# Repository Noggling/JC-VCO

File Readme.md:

# Analog JC Oscillator

Speck for JS Oscillator v1. The first version should be  a proof of concept. Containing a limited amount of features

## Contents

- [Analog JC Oscillator](#analog-jc-oscillator)
  - [Contents](#contents)
  - [Links](#links)
  - [Resources References](#resources-references)

## Links

- [Requirements](./JS-VCO-Requirements.md)
- [JS-VCO Oscillator](./JS-VCO-Oscillator.md)
- [JS-VCO OneVoltOctave](./JC-VCO-OneVoltOctave.md)

- 1v/oct tracing for pitch.
- Core Frequency Adjustment
- Fine Frequency Adjustment
- FM modulation
- PWM Puls With Modulation
  
## Outputs

# Ideas

## Waveshaping through "cheats"

Adjustable Half wave rectifier can be used to fold a Saw into a triangle by reflecting the top by inverting the "overflow" input. This can be achieved by adjusting the amplification of the saw output.

<!-- ## About -->

<!-- TODO -->
## Resources References

<!-- # Build Guide -->

<!-- TODO -->

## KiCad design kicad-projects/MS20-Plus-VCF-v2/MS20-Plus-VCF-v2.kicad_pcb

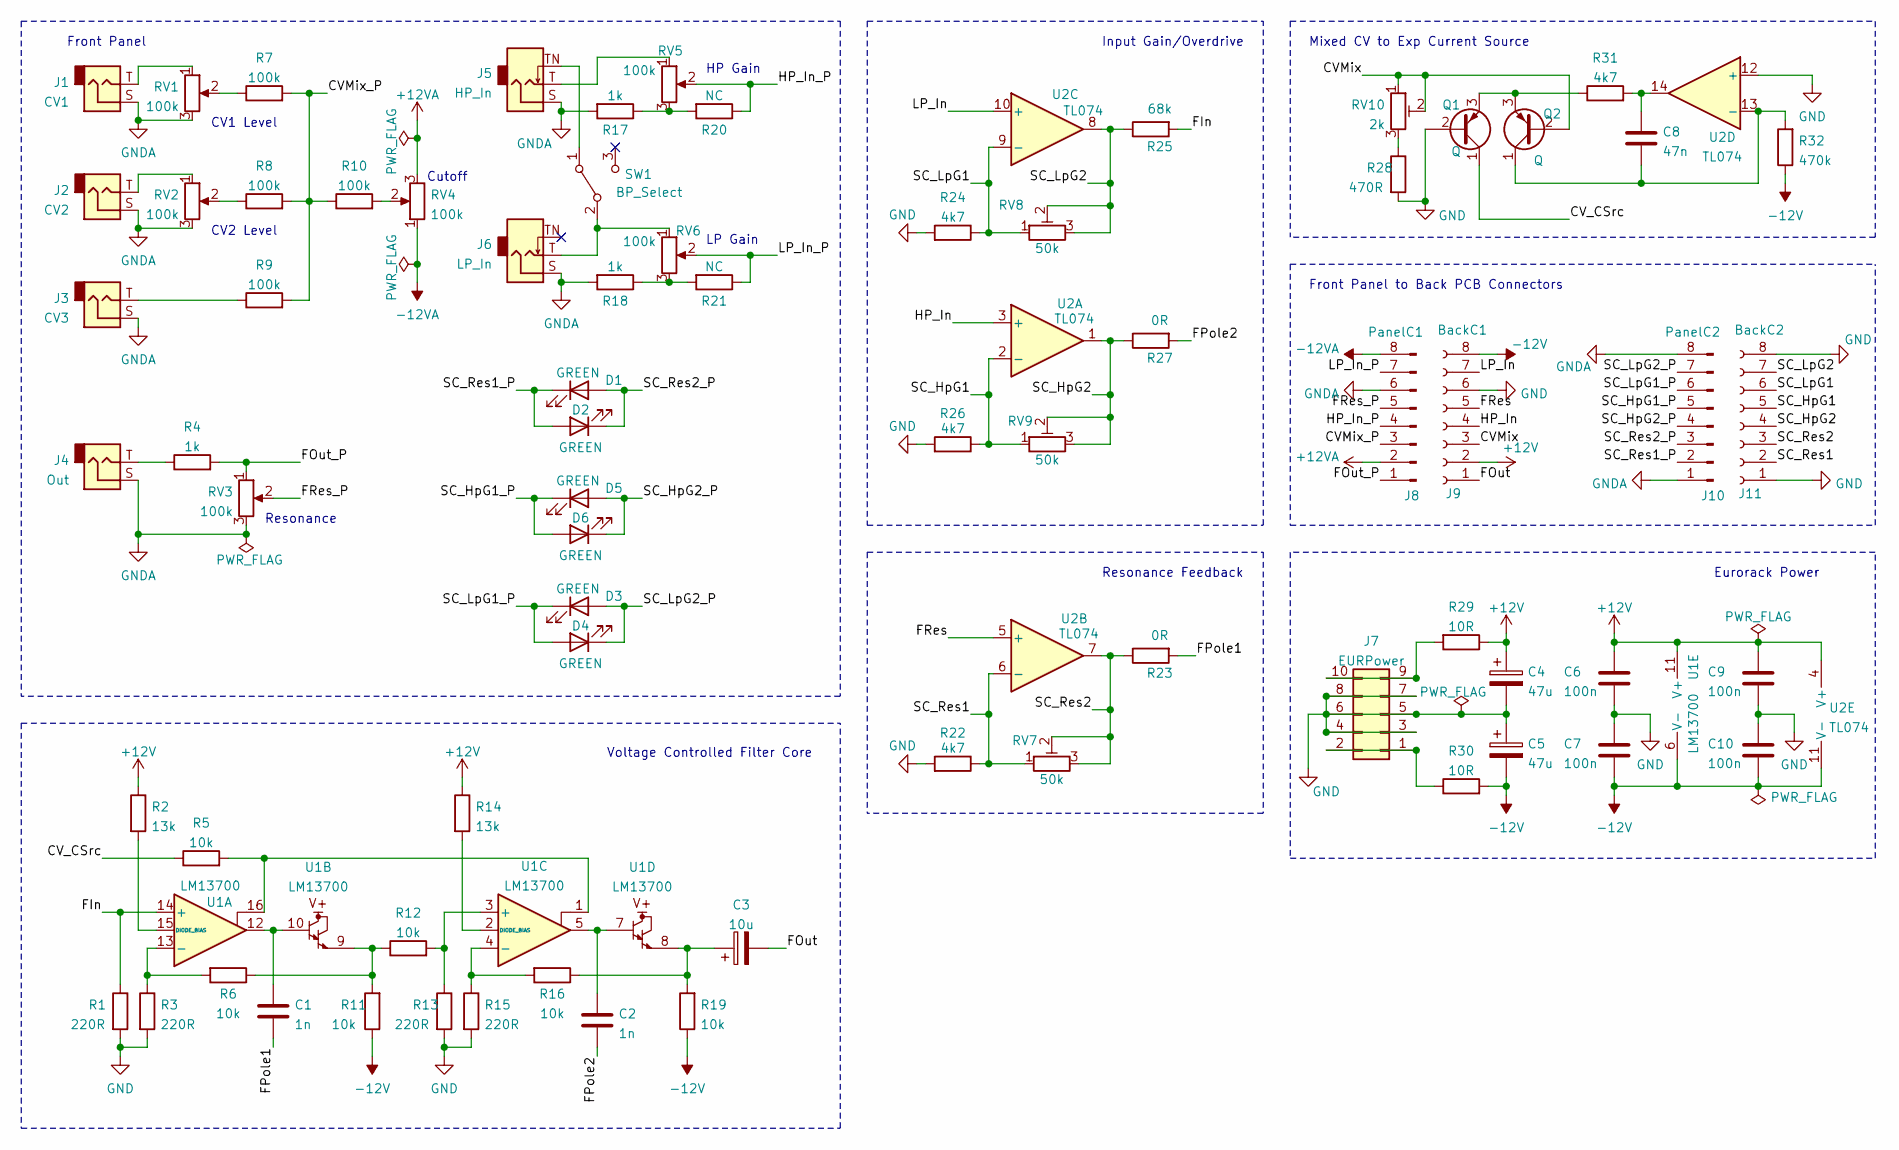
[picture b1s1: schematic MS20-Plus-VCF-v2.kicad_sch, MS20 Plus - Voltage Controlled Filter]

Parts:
C1, C2: 1n; C_Rect_L7.0mm_W3.5mm_P5.00mm
C3: 10u; CP_Radial_D5.0mm_P2.50mm
C4, C5: 47u; CP_Radial_D6.3mm_P2.50mm
C6, C7, C9, C10: 100n; C_Rect_L7.0mm_W3.5mm_P5.00mm
C8: 47n; C_Rect_L7.0mm_W3.5mm_P5.00mm
D1, D2, D3, D4, D5, D6: GREEN; LED_D3.0mm
J1: CV1; Jack_3.5mm_QingPu_WQP-PJ398SM_Vertical_CircularHoles
J2: CV2; Jack_3.5mm_QingPu_WQP-PJ398SM_Vertical_CircularHoles
J3: CV3; Jack_3.5mm_QingPu_WQP-PJ398SM_Vertical_CircularHoles
J4: Out; Jack_3.5mm_QingPu_WQP-PJ398SM_Vertical_CircularHoles
J5: HP_In; Jack_3.5mm_QingPu_WQP-PJ398SM_Vertical_CircularHoles
J6: LP_In; Jack_3.5mm_QingPu_WQP-PJ398SM_Vertical_CircularHoles
J7: EURPower; IDC-Header_2x05_P2.54mm_Vertical
J8: PanelC1; PinHeader_1x08_P2.54mm_Vertical
J9: BackC1; PinSocket_1x08_P2.54mm_Vertical
J10: PanelC2; PinHeader_1x08_P2.54mm_Vertical
J11: BackC2; PinSocket_1x08_P2.54mm_Vertical
Q1, Q2: Q; TO-92_Inline
R1, R3, R13, R15: 220R; R_Axial_DIN0207_L6.3mm_D2.5mm_P7.62mm_Horizontal
R2, R14: 13k; R_Axial_DIN0207_L6.3mm_D2.5mm_P7.62mm_Horizontal
R4, R17, R18: 1k; R_Axial_DIN0207_L6.3mm_D2.5mm_P7.62mm_Horizontal
R5, R6, R11, R12, R16, R19: 10k; R_Axial_DIN0207_L6.3mm_D2.5mm_P7.62mm_Horizontal
R7, R8, R9, R10: 100k; R_Axial_DIN0207_L6.3mm_D2.5mm_P7.62mm_Horizontal
R20, R21: NC; R_Axial_DIN0207_L6.3mm_D2.5mm_P7.62mm_Horizontal
R22, R24, R26, R31: 4k7; R_Axial_DIN0207_L6.3mm_D2.5mm_P7.62mm_Horizontal
R23, R27: 0R; R_Axial_DIN0207_L6.3mm_D2.5mm_P7.62mm_Horizontal
R25: 68k; R_Axial_DIN0207_L6.3mm_D2.5mm_P7.62mm_Horizontal
R28: 470R; R_Axial_DIN0207_L6.3mm_D2.5mm_P7.62mm_Horizontal
R29, R30: 10R; R_Axial_DIN0207_L6.3mm_D2.5mm_P7.62mm_Horizontal
R32: 470k; R_Axial_DIN0207_L6.3mm_D2.5mm_P7.62mm_Horizontal
RV1, RV2, RV3, RV4, RV5, RV6: 100k; Potentiometer_Alpha_RD901F-40-00D_Single_Vertical
RV7, RV8, RV9: 50k; Potentiometer_Bourns_3296W_Vertical
RV10: 2k; Potentiometer_Bourns_3296W_Vertical
SW1: BP_Select; 5mm_rocker_toggle_switch
U1: LM13700; DIP-16_W7.62mm
U2: TL074; DIP-14_W7.62mm

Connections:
+12V: C4.1, C6.1, C9.1, J9.2, R2.1, R14.1, R29.1, U1.11 (V+), U2.4 (V+)
+12VA: J8.2, RV4.3
-12V: C5.2, C7.2, C10.2, J9.8, R11.1, R19.1, R30.2, R32.1, U1.6 (V-), U2.11 (V-)
-12VA: J8.8, RV4.1
/CVMix: J9.3, Q2.2 (B), RV10.1, RV10.2
/CVMix_P: J8.3, R7.2, R8.2, R9.2, R10.1
/CV_CSrc: Q1.1 (C), R5.1
/FIn: R1.1, R25.2, U1.14 (+)
/FOut: C3.2, J9.1
/FOut_P: J8.1, R4.2, RV3.1
/FPole1: C1.2, R23.2
/FPole2: C2.2, R27.2
/FRes: J9.5, U2.5 (+)
/FRes_P: J8.5, RV3.2
/HP_In: J9.4, U2.3 (+)
/HP_In_P: J8.4, R20.1, RV5.2
/LP_In: J9.7, U2.10 (+)
/LP_In_P: J8.7, R21.1, RV6.2
/SC_HpG1: J11.5, R26.1, RV9.1, U2.2 (-)
/SC_HpG1_P: D5.1 (K), D6.2 (A), J10.5
/SC_HpG2: J11.4, R27.1, RV9.2, RV9.3, U2.1
/SC_HpG2_P: D5.2 (A), D6.1 (K), J10.4
/SC_LpG1: J11.6, R24.1, RV8.1, U2.9 (-)
/SC_LpG1_P: D3.1 (K), D4.2 (A), J10.6
/SC_LpG2: J11.7, R25.1, RV8.2, RV8.3, U2.8
/SC_LpG2_P: D3.2 (A), D4.1 (K), J10.7
/SC_Res1: J11.2, R22.1, RV7.1, U2.6 (-)
/SC_Res1_P: D1.1 (K), D2.2 (A), J10.2
/SC_Res2: J11.3, R23.1, RV7.2, RV7.3, U2.7
/SC_Res2_P: D1.2 (A), D2.1 (K), J10.3
GND: C4.2, C5.1, C6.2, C7.1, C9.2, C10.1, J7.3, J7.4, J7.5, J7.6, J7.7, J7.8, J9.6, J11.1, J11.8, Q1.2 (B), R1.2, R3.2, R13.2, R15.2, R22.2, R24.2, R26.2, R28.2, U2.12 (+)
GNDA: J1.S, J2.S, J3.S, J4.S, J5.S, J6.S, J8.6, J10.1, J10.8, R17.2, R18.2, RV1.3, RV2.3, RV3.3
unnamed: C1.1, U1.10, U1.12
unnamed: C2.1, U1.5, U1.7
unnamed: C3.1, R16.1, R19.2, U1.8
unnamed: C8.1, R31.2, U2.14
unnamed: C8.2, Q2.1 (C), R32.2, U2.13 (-)
unnamed: J1.T, RV1.1
unnamed: J2.T, RV2.1
unnamed: J3.T, R9.1
unnamed: J4.T, R4.1
unnamed: J5.T, RV5.1
unnamed: J5.TN, SW1.1 (A)
unnamed: J6.T, RV6.1, SW1.2 (B)
unnamed: J7.1, J7.2, R30.1
unnamed: J7.9, J7.10, R29.2
unnamed: Q1.3 (E), Q2.3 (E), R31.1
unnamed: R2.2, U1.15 (DIODE_BIAS)
unnamed: R3.1, R6.2, U1.13 (-)
unnamed: R5.2, U1.1, U1.16
unnamed: R7.1, RV1.2
unnamed: R8.1, RV2.2
unnamed: R10.2, RV4.2
unnamed: R6.1, R11.2, R12.1, U1.9
unnamed: R12.2, R13.1, U1.3 (+)
unnamed: R14.2, U1.2 (DIODE_BIAS)
unnamed: R15.1, R16.2, U1.4 (-)
unnamed: R17.1, R20.2, RV5.3
unnamed: R18.1, R21.2, RV6.3
unnamed: R28.1, RV10.3

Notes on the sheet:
Front Panel
CV1 Level
CV2 Level
Resonance
Cutoff
Voltage Controlled Filter Core
HP Gain
LP Gain
Input Gain/Overdrive
Resonance Feedback
Mixed CV to Exp Current Source
Front Panel to Back PCB Connectors
Eurorack Power

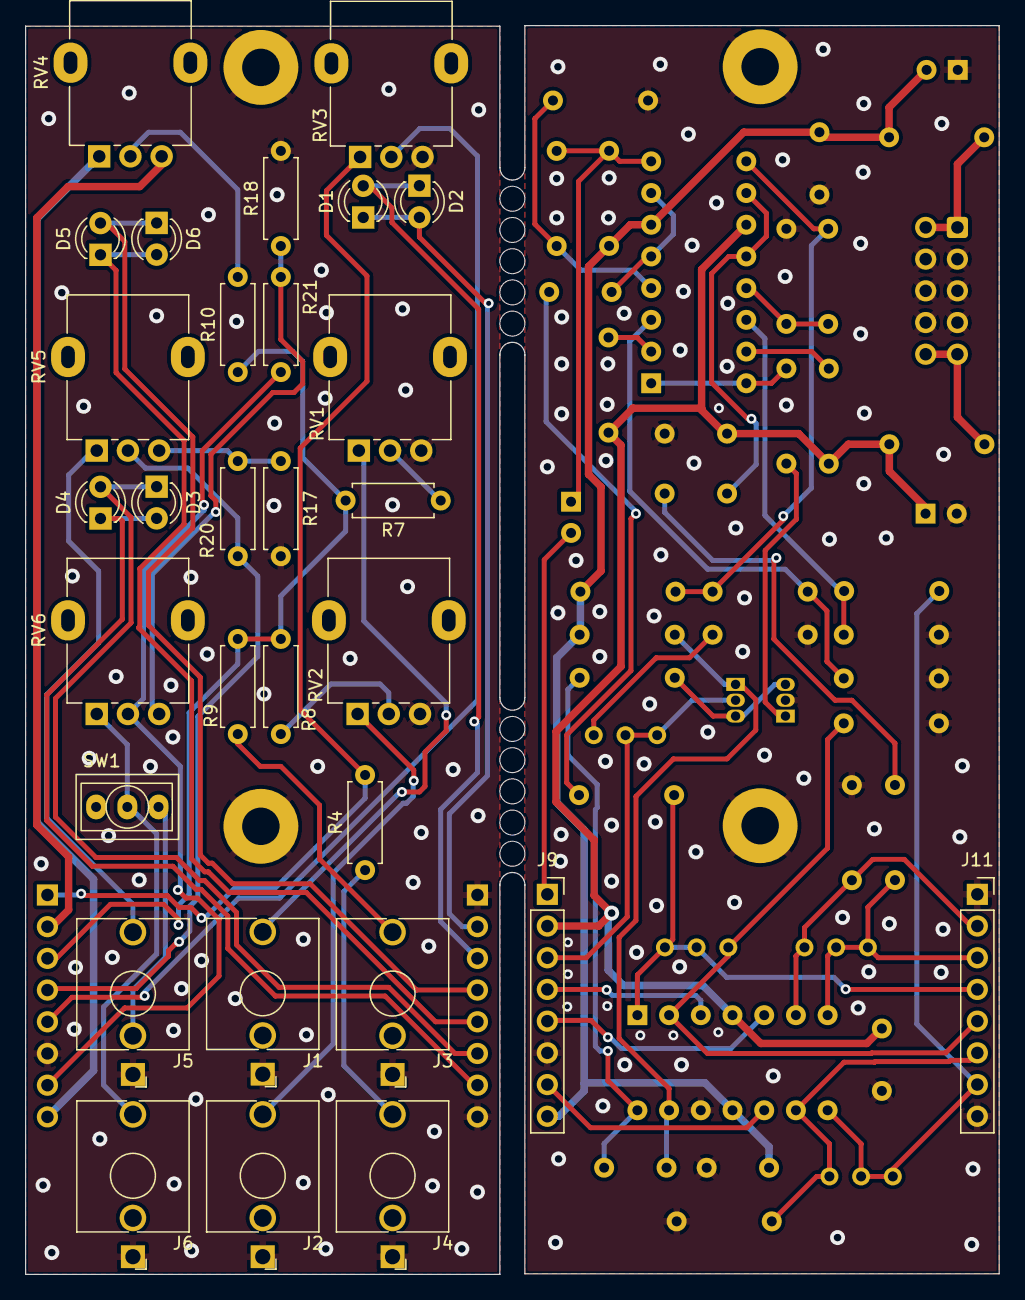
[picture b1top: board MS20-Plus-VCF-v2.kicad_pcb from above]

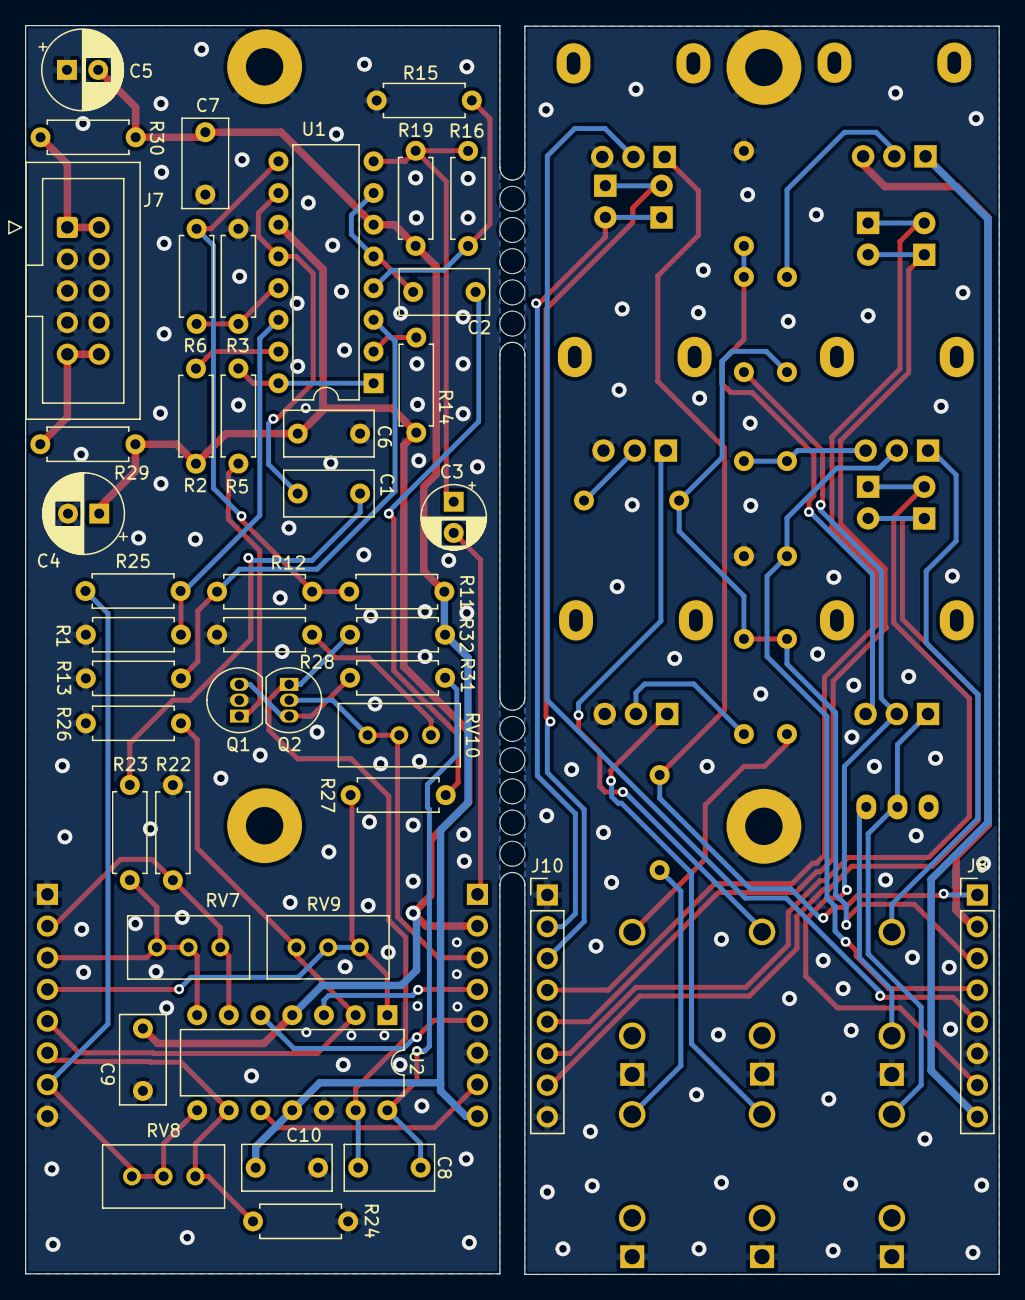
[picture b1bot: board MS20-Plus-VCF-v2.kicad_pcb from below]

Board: 2 copper layers, 78.0 x 100.1 mm, 74 parts (44 on the bottom side), 60 nets.

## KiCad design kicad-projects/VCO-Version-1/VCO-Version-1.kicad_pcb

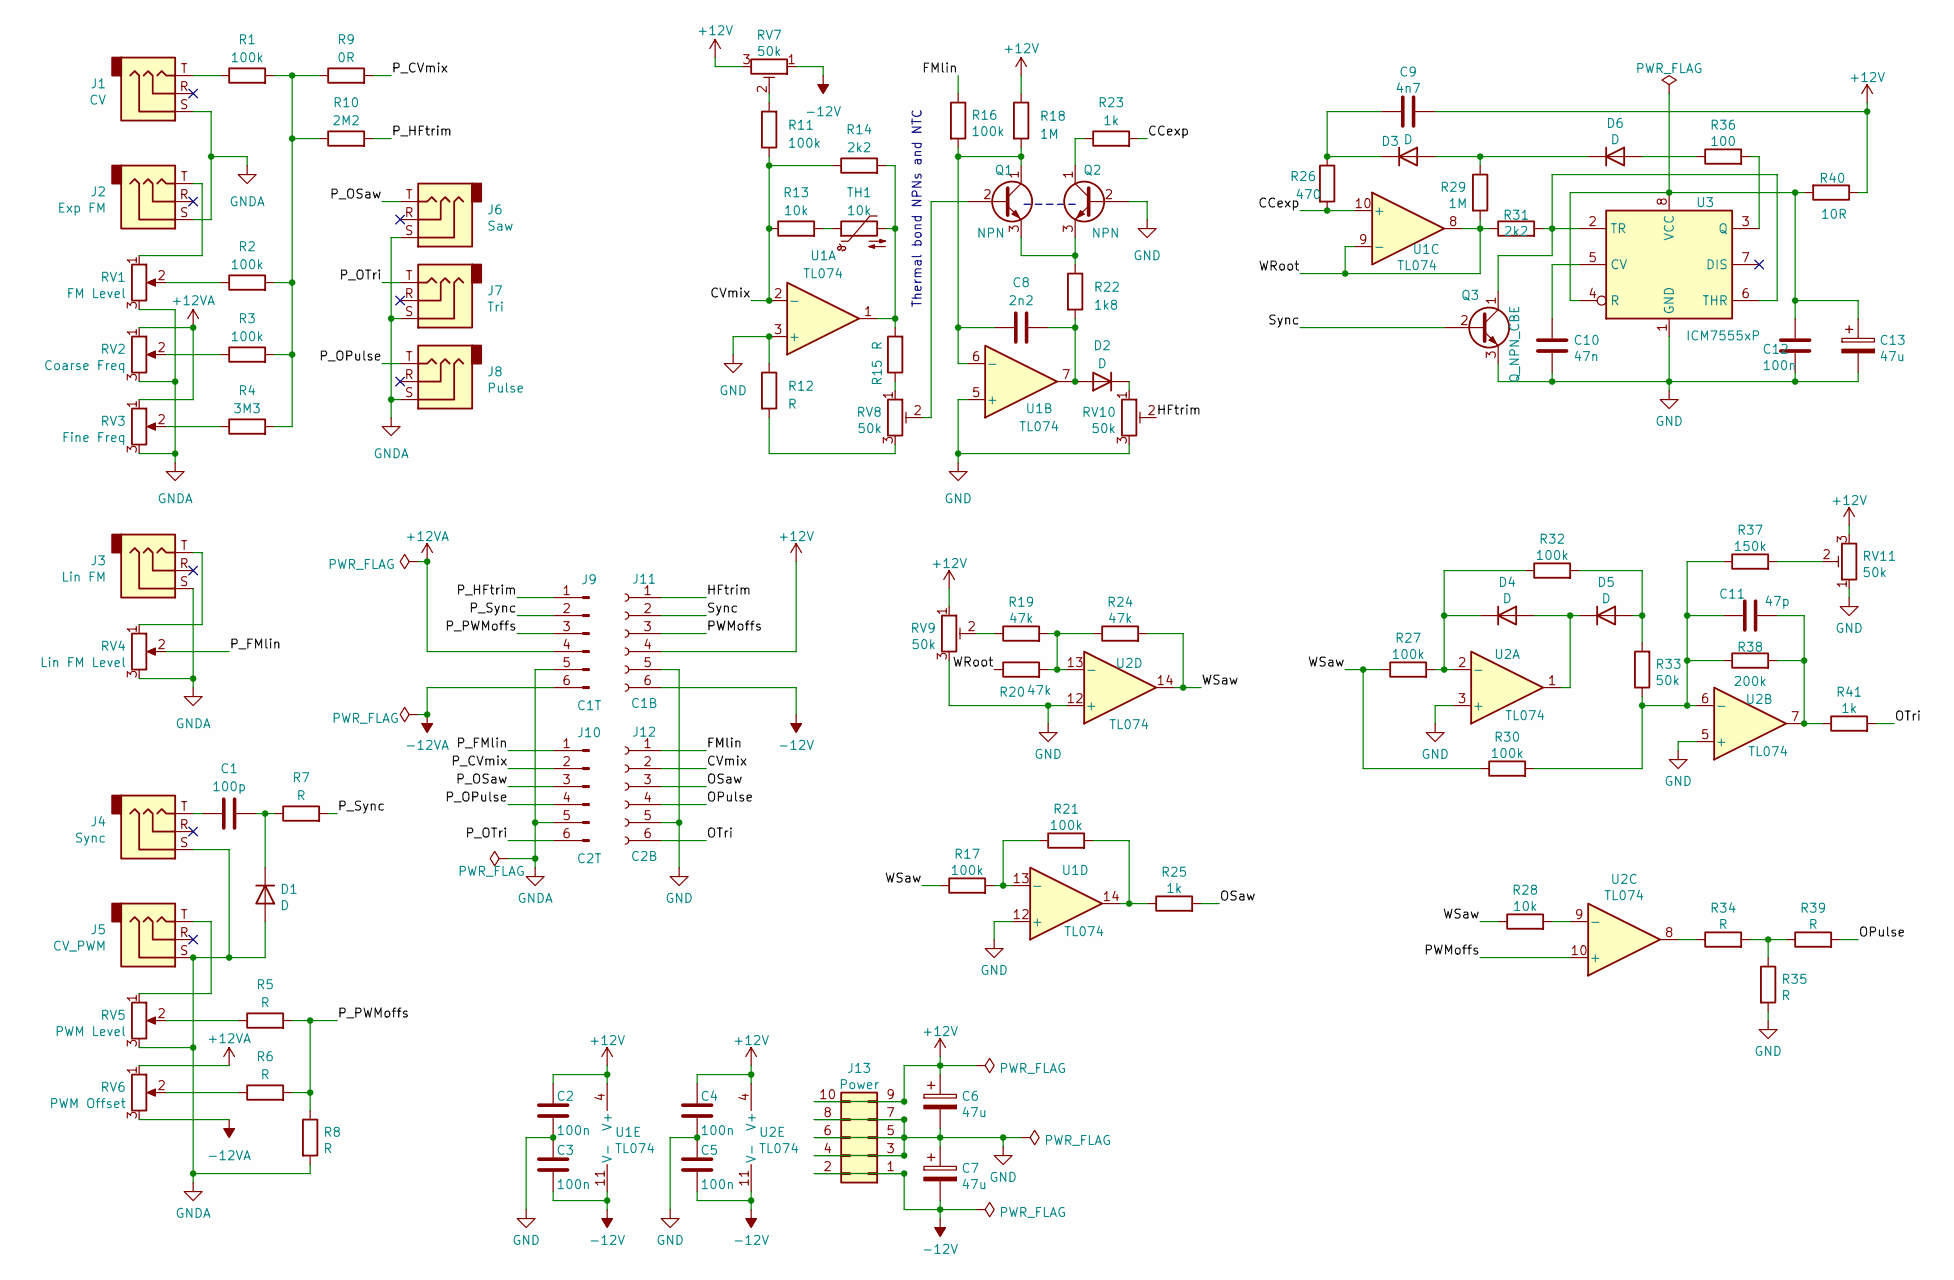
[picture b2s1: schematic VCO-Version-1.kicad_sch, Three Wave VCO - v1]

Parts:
C1: 100p; C_Rect_L7.0mm_W3.5mm_P5.00mm
C2, C3, C4, C5, C12: 100n; C_Rect_L7.0mm_W3.5mm_P5.00mm
C6, C7, C13: 47u; CP_Radial_D6.3mm_P2.50mm
C8: 2n2; C_Rect_L7.0mm_W3.5mm_P5.00mm
C9: 4n7; C_Rect_L7.0mm_W3.5mm_P5.00mm
C10: 47n; C_Rect_L7.0mm_W3.5mm_P5.00mm
C11: 47p; C_Rect_L7.0mm_W3.5mm_P5.00mm
D1, D2, D3, D4, D5, D6: D; D_DO-35_SOD27_P7.62mm_Horizontal
J1: CV; Jack_3.5mm_QingPu_WQP-PJ398SM_Vertical_CircularHoles
J2: Exp FM; Jack_3.5mm_QingPu_WQP-PJ398SM_Vertical_CircularHoles
J3: Lin FM; Jack_3.5mm_QingPu_WQP-PJ398SM_Vertical_CircularHoles
J4: Sync; Jack_3.5mm_QingPu_WQP-PJ398SM_Vertical_CircularHoles
J5: CV_PWM; Jack_3.5mm_QingPu_WQP-PJ398SM_Vertical_CircularHoles
J6: Saw; Jack_3.5mm_QingPu_WQP-PJ398SM_Vertical_CircularHoles
J7: Tri; Jack_3.5mm_QingPu_WQP-PJ398SM_Vertical_CircularHoles
J8: Pulse; Jack_3.5mm_QingPu_WQP-PJ398SM_Vertical_CircularHoles
J9: C1T; PinHeader_1x06_P2.54mm_Vertical
J10: C2T; PinHeader_1x06_P2.54mm_Vertical
J11: C1B; PinSocket_1x06_P2.54mm_Vertical
J12: C2B; PinSocket_1x06_P2.54mm_Vertical
J13: Power; IDC-Header_2x05_P2.54mm_Vertical
Q1, Q2: NPN; TO-92_Inline
Q3: Q_NPN_CBE; TO-92_Inline
R1, R2, R3, R11, R16, R17, R21, R27, R30, R32: 100k; R_Axial_DIN0207_L6.3mm_D2.5mm_P7.62mm_Horizontal
R4: 3M3; R_Axial_DIN0207_L6.3mm_D2.5mm_P7.62mm_Horizontal
R5, R6, R7, R8, R12, R15, R34, R35, R39: R; R_Axial_DIN0207_L6.3mm_D2.5mm_P7.62mm_Horizontal
R9: 0R; R_Axial_DIN0207_L6.3mm_D2.5mm_P7.62mm_Horizontal
R10: 2M2; R_Axial_DIN0207_L6.3mm_D2.5mm_P7.62mm_Horizontal
R13, R28: 10k; R_Axial_DIN0207_L6.3mm_D2.5mm_P7.62mm_Horizontal
R14, R31: 2k2; R_Axial_DIN0207_L6.3mm_D2.5mm_P7.62mm_Horizontal
R18, R29: 1M; R_Axial_DIN0207_L6.3mm_D2.5mm_P7.62mm_Horizontal
R19, R20, R24: 47k; R_Axial_DIN0207_L6.3mm_D2.5mm_P7.62mm_Horizontal
R22: 1k8; R_Axial_DIN0207_L6.3mm_D2.5mm_P7.62mm_Horizontal
R23, R25, R41: 1k; R_Axial_DIN0207_L6.3mm_D2.5mm_P7.62mm_Horizontal
R26: 470; R_Axial_DIN0207_L6.3mm_D2.5mm_P7.62mm_Horizontal
R33: 50k; R_Axial_DIN0207_L6.3mm_D2.5mm_P7.62mm_Horizontal
R36: 100; R_Axial_DIN0207_L6.3mm_D2.5mm_P7.62mm_Horizontal
R37: 150k; R_Axial_DIN0207_L6.3mm_D2.5mm_P7.62mm_Horizontal
R38: 200k; R_Axial_DIN0207_L6.3mm_D2.5mm_P7.62mm_Horizontal
R40: 10R; R_Axial_DIN0207_L6.3mm_D2.5mm_P7.62mm_Horizontal
RV1: FM Level; Potentiometer_Alpha_RD901F-40-00D_Single_Vertical
RV2: Coarse Freq; Potentiometer_Alpha_RD901F-40-00D_Single_Vertical
RV3: Fine Freq; Potentiometer_Alpha_RD901F-40-00D_Single_Vertical
RV4: Lin FM Level; Potentiometer_Alpha_RD901F-40-00D_Single_Vertical
RV5: PWM Level; Potentiometer_Alpha_RD901F-40-00D_Single_Vertical
RV6: PWM Offset; Potentiometer_Alpha_RD901F-40-00D_Single_Vertical
RV7, RV8, RV9, RV10, RV11: 50k; Potentiometer_Bourns_3296W_Vertical
TH1: 10k; R_Axial_DIN0207_L6.3mm_D2.5mm_P2.54mm_Vertical
U1, U2: TL074; DIP-14_W7.62mm_Socket
U3: ICM7555xP; DIP-8_W7.62mm

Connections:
+12V: C2.1, C4.1, C6.1, C9.2, J11.4, J13.9, J13.10, R18.1, R40.1, RV7.3, RV9.1, RV11.3, U1.4 (V+), U2.4 (V+)
+12VA: J9.4, RV2.1, RV3.1, RV6.1
-12V: C3.2, C5.2, C7.2, J11.6, J13.1, J13.2, RV7.1, U1.11 (V-), U2.11 (V-)
-12VA: J9.6, RV6.3
/CCexp: R23.2, R26.2, U1.10 (+)
/CVmix: J12.2, R11.1, R13.1, R14.1, U1.2 (-)
/FMlin: J12.1, R16.1
/HFtrim: J11.1, RV10.2
/OPulse: J12.4, R39.2
/OSaw: J12.3, R25.2
/OTri: J12.6, R41.2
/PWMoffs: J11.3, U2.10 (+)
/P_CVmix: J10.2, R9.2
/P_FMlin: J10.1, RV4.2
/P_HFtrim: J9.1, R10.2
/P_OPulse: J8.T, J10.4
/P_OSaw: J6.T, J10.3
/P_OTri: J7.T, J10.6
/P_PWMoffs: J9.3, R5.2, R6.2, R8.1
/P_Sync: J9.2, R7.2
/Sync: J11.2, Q3.2 (B)
/WRoot: R20.1, R29.2, R31.1, U1.8, U1.9 (-)
/WSaw: R17.1, R24.2, R27.1, R28.1, R30.1, U2.14
GND: C2.2, C3.1, C4.2, C5.1, C6.2, C7.1, C10.2, C12.2, C13.2, J11.5, J12.5, J13.3, J13.4, J13.5, J13.6, J13.7, J13.8, Q2.2 (B), Q3.3 (E), R12.1, R35.2, RV9.3, RV10.3, RV11.1, U1.3 (+), U1.5 (+), U1.12 (+), U2.3 (+), U2.5 (+), U2.12 (+), U3.1 (GND)
GNDA: D1.2 (A), J1.S, J2.S, J3.S, J4.S, J5.S, J6.S, J7.S, J8.S, J9.5, J10.5, R8.2, RV1.3, RV2.3, RV3.3, RV4.3, RV5.3
unnamed: C1.1, J4.T
unnamed: C1.2, D1.1 (K), R7.1
unnamed: C8.1, Q1.1 (C), R16.2, R18.2, U1.6 (-)
unnamed: C8.2, D2.2 (A), R22.2, U1.7
unnamed: C9.1, D3.1 (K), R26.1
unnamed: C10.1, U3.5 (CV)
unnamed: C11.1, R30.2, R33.1, R37.1, R38.1, U2.6 (-)
unnamed: C11.2, R38.2, R41.1, U2.7
unnamed: C12.1, C13.1, R40.2, U3.4 (R), U3.8 (VCC)
unnamed: D2.1 (K), RV10.1
unnamed: D3.2 (A), D6.1 (K), R29.1
unnamed: D4.1 (K), R27.2, R32.1, U2.2 (-)
unnamed: D4.2 (A), D5.1 (K), U2.1
unnamed: D5.2 (A), R32.2, R33.2
unnamed: D6.2 (A), R36.1
unnamed: J1.T, R1.1
unnamed: J2.T, RV1.1
unnamed: J3.T, RV4.1
unnamed: J5.T, RV5.1
unnamed: Q1.2 (B), RV8.2
unnamed: Q1.3 (E), Q2.3 (E), R22.1
unnamed: Q2.1 (C), R23.1
unnamed: Q3.1 (C), R31.2, U3.2 (TR), U3.6 (THR)
unnamed: R1.2, R2.2, R3.2, R4.2, R9.1, R10.1
unnamed: R2.1, RV1.2
unnamed: R3.1, RV2.2
unnamed: R4.1, RV3.2
unnamed: R5.1, RV5.2
unnamed: R6.1, RV6.2
unnamed: R11.2, RV7.2
unnamed: R12.2, RV8.3
unnamed: R13.2, TH1.1
unnamed: R14.2, R15.2, TH1.2, U1.1
unnamed: R15.1, RV8.1
unnamed: R17.2, R21.1, U1.13 (-)
unnamed: R19.1, RV9.2
unnamed: R19.2, R20.2, R24.1, U2.13 (-)
unnamed: R21.2, R25.1, U1.14
unnamed: R28.2, U2.9 (-)
unnamed: R34.1, U2.8
unnamed: R34.2, R35.1, R39.1
unnamed: R36.2, U3.3 (Q)
unnamed: R37.2, RV11.2

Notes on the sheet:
Thermal bond NPNs and NTC
-----

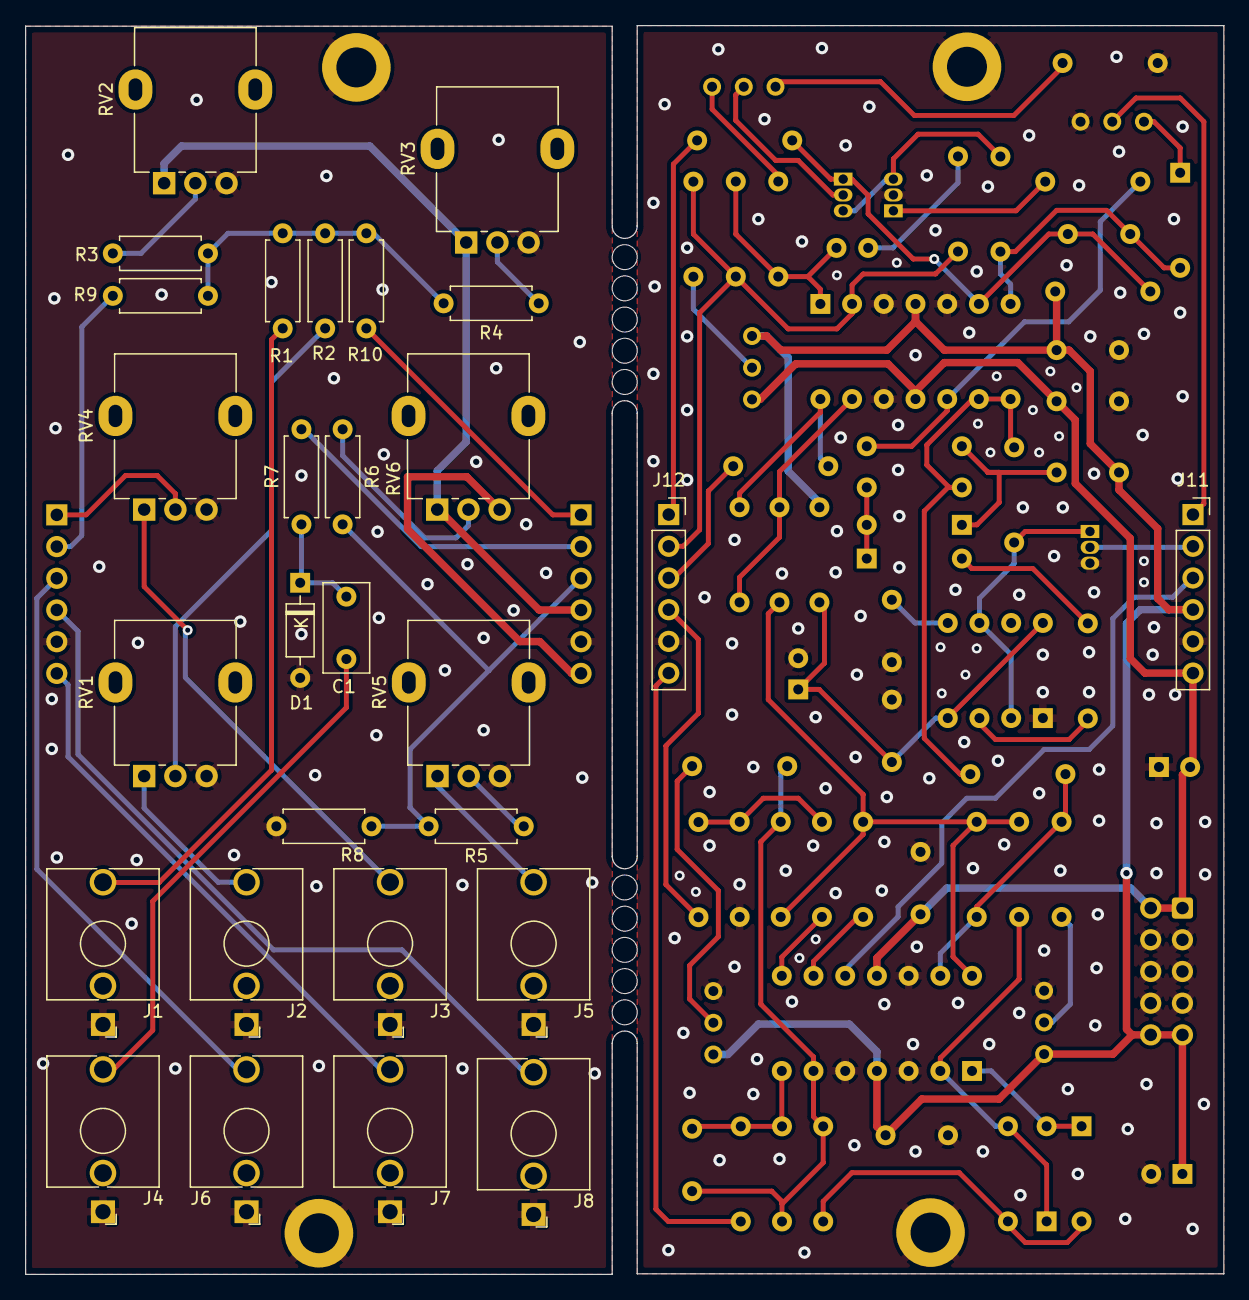
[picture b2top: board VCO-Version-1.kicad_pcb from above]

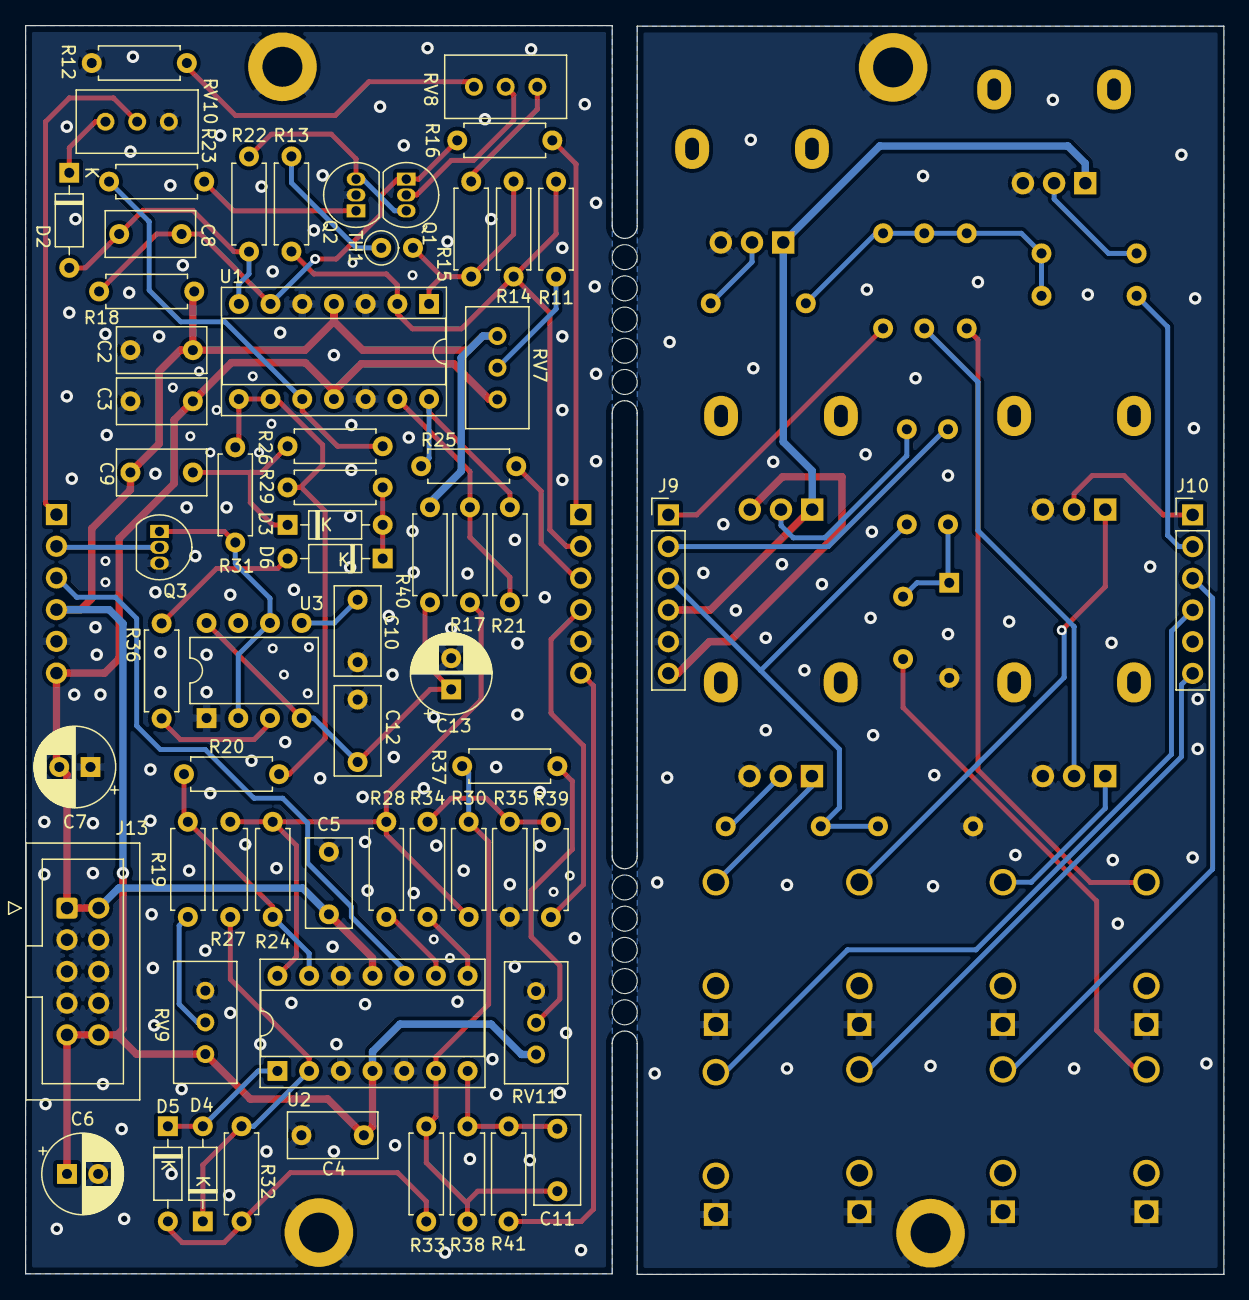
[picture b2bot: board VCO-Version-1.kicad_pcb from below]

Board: 2 copper layers, 96.0 x 100.0 mm, 91 parts (63 on the bottom side), 68 nets.

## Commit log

2021-01-13 init Readme file
2021-01-13 Added an interesting design and a test simulation
2021-01-13 Added wavefolder schematic as well.
2021-01-19 Voltage splitter circuit
2021-01-20 Added two oscillator simulations
2021-01-20 Added another interesting circuit, which seemingly reverses the waveform on a sync
2021-01-20 Added simulation for expo converter.
2021-01-20 Refacror and added Ocilator file.
2021-01-20 Back and Contents
2021-01-21 1VO Circuit
2021-01-21 Rename
2021-01-21 link fix
2021-01-21 link update
2021-01-22 Added KiCad Nightly project for first VCO design
2021-01-25 Added schematic for MS20 VCF.
2021-01-25 Finalized the VCF schematics
2021-01-25 Fixed title in Schematic
2021-05-19 Added some simulations for Falstad, showcasing some design tests
2021-05-26 Committed some uncommitted changes
2021-05-27 Added new simulation of a 40106 based oscillator
2021-05-27 Added KiCAD project for the VCO-v1
2021-06-03 Updated the supersaw simulation
2021-06-03 Updated with PWM example.
2021-06-09 Completed schematic for VCO-1
2021-06-16 Worked more on VCO1 PCB
2021-06-16 More work on layout on PCB
2021-06-20 Added completed PCB layout which will likely be ordered.
2021-06-23 Added new VFC project. Added gerbers which are used for production of the VCO.
2021-06-23 Fixed minor connection issue
2021-06-23 More nitpicking
2021-06-23 Minor cleanups
2021-06-25 Added PCB for MS20 filter, and BOM for VCO
2021-06-25 More work on the MS20 VCF. Closing in on a final placement.
2021-06-26 Tidied up
2021-06-27 Almost done with main routing
2021-06-27 Finished the layout
2021-06-27 Minor modifications for silkscreen
2021-06-28 Added gerbers and final updates before ordering
2021-07-06 Added simulation of seamless transition of linear to exponetial VCA control voltage
